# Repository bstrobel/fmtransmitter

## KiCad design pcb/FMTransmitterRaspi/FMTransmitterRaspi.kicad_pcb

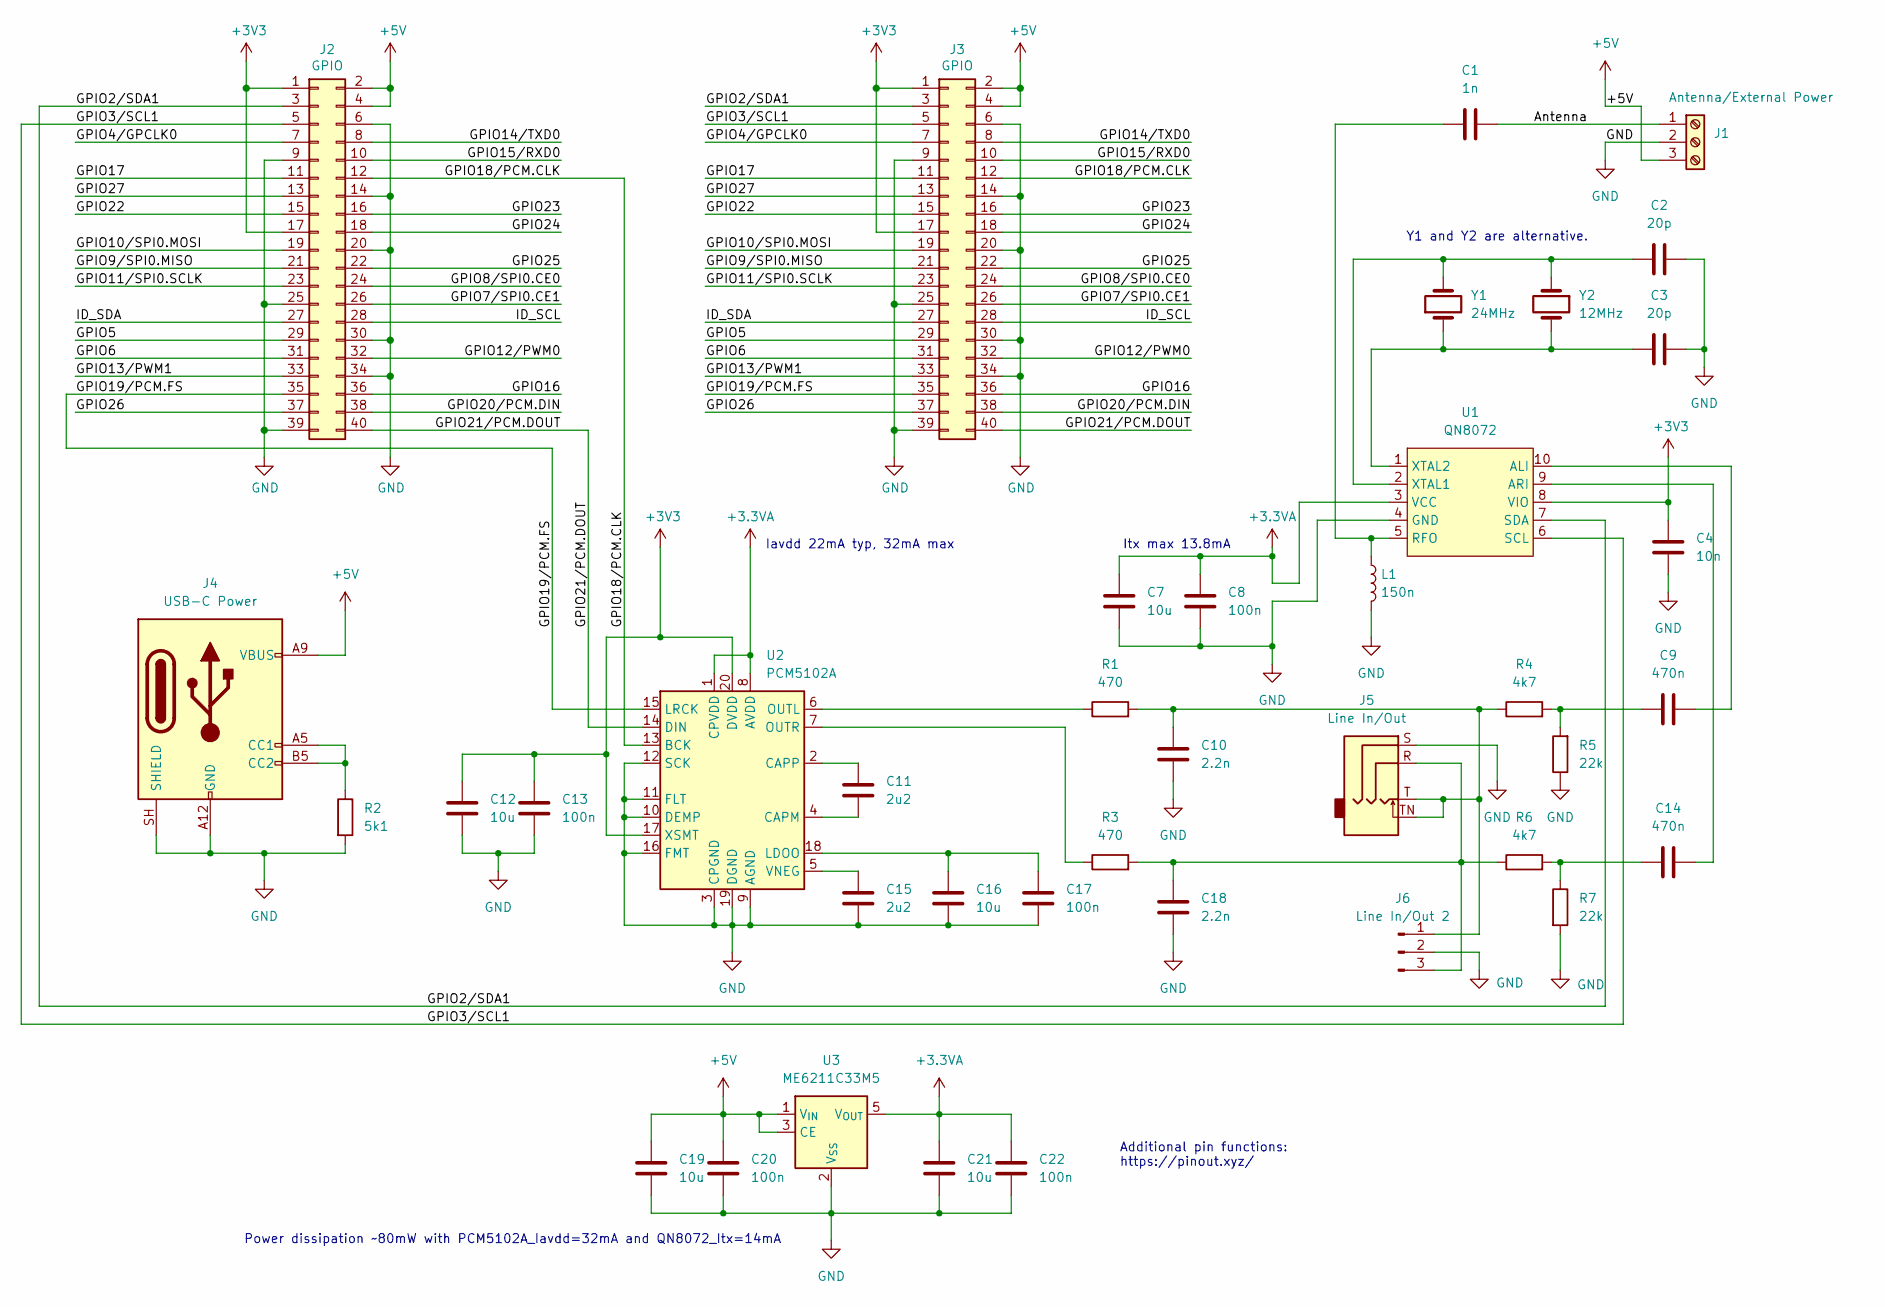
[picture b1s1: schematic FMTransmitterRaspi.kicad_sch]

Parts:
C1: 1n; C_0603_1608Metric_Pad1.08x0.95mm_HandSolder
C2, C3: 20p; C_0603_1608Metric_Pad1.08x0.95mm_HandSolder
C4: 10n; C_0603_1608Metric_Pad1.08x0.95mm_HandSolder
C7, C12, C16: 10u; C_0603_1608Metric_Pad1.08x0.95mm_HandSolder
C8, C13, C17, C20, C22: 100n; C_0603_1608Metric_Pad1.08x0.95mm_HandSolder
C9, C14: 470n; C_Rect_L7.2mm_W3.5mm_P5.00mm
C10, C18: 2.2n; C_Rect_L9.0mm_W2.7mm_P7.50mm_MKT
C11, C15: 2u2; C_0603_1608Metric_Pad1.08x0.95mm_HandSolder
C19, C21: 10u; C_0805_2012Metric_Pad1.18x1.45mm_HandSolder
J1: Antenna/External Power; TerminalBlock_MaiXu_MX126-5.0-03P_1x03_P5.00mm
J2: GPIO; PinSocket_2x20_P2.54mm_Vertical
J3: GPIO; PinHeader_2x20_P2.54mm_Vertical
J4: USB-C Power; USB_C_Receptacle_HRO_TYPE-C-31-M-17
J5: Line In/Out; Jack_3.5mm_PJ327A_Horizontal
J6: Line In/Out 2; PinHeader_1x03_P2.54mm_Vertical
L1: 150n; L_0805_2012Metric_Pad1.05x1.20mm_HandSolder
R1, R3: 470; R_0603_1608Metric_Pad0.98x0.95mm_HandSolder
R2: 5k1; R_0603_1608Metric_Pad0.98x0.95mm_HandSolder
R4, R6: 4k7; R_0603_1608Metric_Pad0.98x0.95mm_HandSolder
R5, R7: 22k; R_0603_1608Metric_Pad0.98x0.95mm_HandSolder
U1: QN8072; MSOP-10_3x3mm_P0.5mm
U2: PCM5102A; TSSOP-20_4.4x6.5mm_P0.65mm
U3: ME6211C33M5; SOT-23-5
Y1: 24MHz; Crystal_HC18-U_Vertical
Y2: 12MHz; Crystal_DS15_D1.5mm_L5.0mm_Horizontal_1EP_style1

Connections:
+3.3VA: C7.1, C8.1, C21.1, C22.1, U1.3 (VCC), U2.1 (CPVDD), U2.8 (AVDD), U3.5 (V_{OUT})
+3V3: C4.1, C12.1, C13.1, J2.1, J2.17, J3.1, J3.17, U1.8 (VIO), U2.17 (XSMT), U2.20 (DVDD)
+5V: C19.1, C20.1, J1.3, J2.2, J2.4, J3.2, J3.4, J4.A9 (VBUS), J4.B9 (VBUS), U3.1 (V_{IN}), U3.3 (CE)
/Antenna: C1.2, J1.1
/GPIO2/SDA1: J2.3, J3.3, U1.7 (SDA)
/GPIO3/SCL1: J2.5, J3.5, U1.6 (SCL)
/GPIO4/GPCLK0: J2.7, J3.7
/GPIO5: J2.29, J3.29
/GPIO6: J2.31, J3.31
/GPIO7/SPI0.CE1: J2.26, J3.26
/GPIO8/SPI0.CE0: J2.24, J3.24
/GPIO9/SPI0.MISO: J2.21, J3.21
/GPIO10/SPI0.MOSI: J2.19, J3.19
/GPIO11/SPI0.SCLK: J2.23, J3.23
/GPIO12/PWM0: J2.32, J3.32
/GPIO13/PWM1: J2.33, J3.33
/GPIO14/TXD0: J2.8, J3.8
/GPIO15/RXD0: J2.10, J3.10
/GPIO16: J2.36, J3.36
/GPIO17: J2.11, J3.11
/GPIO18/PCM.CLK: J2.12, J3.12, U2.13 (BCK)
/GPIO19/PCM.FS: J2.35, J3.35, U2.15 (LRCK)
/GPIO20/PCM.DIN: J2.38, J3.38
/GPIO21/PCM.DOUT: J2.40, J3.40, U2.14 (DIN)
/GPIO22: J2.15, J3.15
/GPIO23: J2.16, J3.16
/GPIO24: J2.18, J3.18
/GPIO25: J2.22, J3.22
/GPIO26: J2.37, J3.37
/GPIO27: J2.13, J3.13
/ID_SCL: J2.28, J3.28
/ID_SDA: J2.27, J3.27
GND: C2.2, C3.2, C4.2, C7.2, C8.2, C10.2, C12.2, C13.2, C15.2, C16.2, C17.2, C18.2, C19.2, C20.2, C21.2, C22.2, J1.2, J2.6, J2.9, J2.14, J2.20, J2.25, J2.30, J2.34, J2.39, J3.6, J3.9, J3.14, J3.20, J3.25, J3.30, J3.34, J3.39, J4.A12 (GND), J4.B12 (GND), J4.SH (SHIELD), J5.S, J6.2, L1.2, R2.2, R5.1, R7.2, U1.4 (GND), U2.3 (CPGND), U2.9 (AGND), U2.10 (DEMP), U2.11 (FLT), U2.12 (SCK), U2.16 (FMT), U2.19 (DGND), U3.2 (V_{SS})
unnamed: C9.1, R4.2, R5.2
unnamed: C14.1, R6.2, R7.1
unnamed: J4.A5 (CC1), J4.B5 (CC2), R2.1
unnamed: C10.1, J5.T, J5.TN, J6.1, R1.2, R4.1
unnamed: C18.1, J5.R, J6.3, R3.2, R6.1
unnamed: C9.2, U1.10 (ALI)
unnamed: C14.2, U1.9 (ARI)
unnamed: C1.1, L1.1, U1.5 (RFO)
unnamed: C2.1, U1.2 (XTAL1), Y1.2, Y2.1
unnamed: C3.1, U1.1 (XTAL2), Y1.1, Y2.2
unnamed: C11.2, U2.4 (CAPM)
unnamed: C11.1, U2.2 (CAPP)
unnamed: C16.1, C17.1, U2.18 (LDOO)
unnamed: R1.1, U2.6 (OUTL)
unnamed: R3.1, U2.7 (OUTR)
unnamed: C15.1, U2.5 (VNEG)

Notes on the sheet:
Y1 and Y2 are alternative.
Itx max 13.8mA
Power dissipation ~80mW with PCM5102A_Iavdd=32mA and QN8072_Itx=14mA
Iavdd 22mA typ, 32mA max
Additional pin functions: https://pinout.xyz/

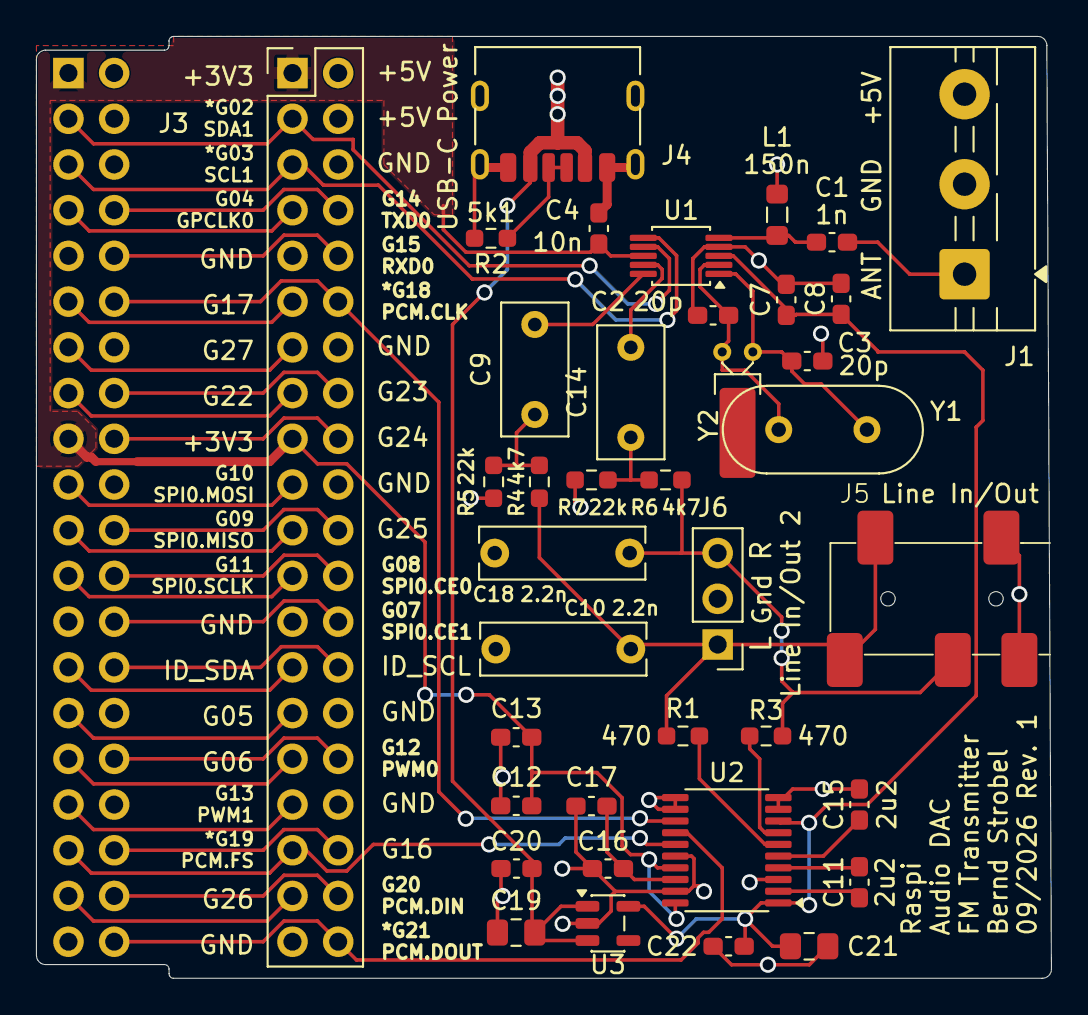
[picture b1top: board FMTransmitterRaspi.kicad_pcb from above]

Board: 2 copper layers, 56.4 x 52.3 mm, 39 parts (1 on the bottom side), 49 nets.

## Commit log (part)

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2026-03-29 Initial working version
2026-04-03 Enums, recalibrate
2026-04-03 Moved constants definitions out of main class
2026-04-03 completed basic functionality
2026-04-19 Command line interface added, get_state refactored, state parsed into class variables
